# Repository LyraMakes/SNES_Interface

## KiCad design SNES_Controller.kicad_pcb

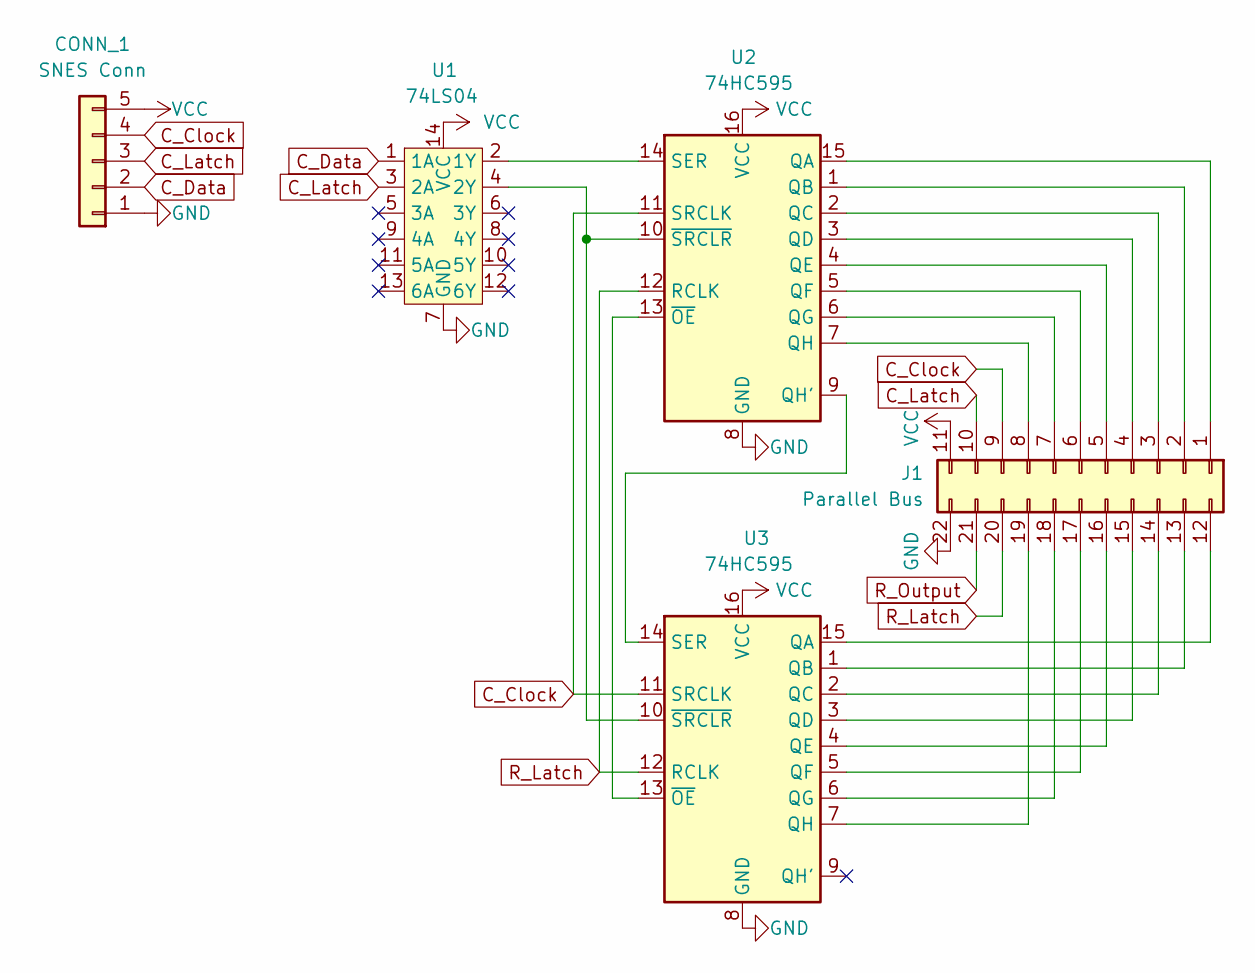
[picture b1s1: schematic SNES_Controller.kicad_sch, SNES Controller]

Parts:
CONN_1: SNES Conn; PinHeader_1x05_P2.54mm_Vertical
J1: Parallel Bus; PinHeader_2x11_P2.54mm_Vertical
U1: 74LS04; DIP-14_W7.62mm
U2, U3: 74HC595; DIP-16_W7.62mm

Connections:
C_Clock: CONN_1.4, J1.9, U2.11 (SRCLK), U3.11 (SRCLK)
C_Data: CONN_1.2, U1.1 (1A)
C_Latch: CONN_1.3, J1.10, U1.3 (2A)
GND: CONN_1.1, J1.22, U1.7 (GND), U2.8 (GND), U3.8 (GND)
unnamed: J1.1, U2.15 (QA)
unnamed: J1.2, U2.1 (QB)
unnamed: J1.3, U2.2 (QC)
unnamed: J1.4, U2.3 (QD)
unnamed: J1.5, U2.4 (QE)
unnamed: J1.6, U2.5 (QF)
unnamed: J1.7, U2.6 (QG)
unnamed: J1.8, U2.7 (QH)
unnamed: J1.12, U3.15 (QA)
unnamed: J1.13, U3.1 (QB)
unnamed: J1.14, U3.2 (QC)
unnamed: J1.15, U3.3 (QD)
unnamed: J1.16, U3.4 (QE)
unnamed: J1.17, U3.5 (QF)
unnamed: J1.18, U3.6 (QG)
unnamed: J1.19, U3.7 (QH)
unnamed: U1.2 (1Y), U2.14 (SER)
unnamed: U2.9 (QH'), U3.14 (SER)
unnamed: U1.4 (2Y), U2.10 (~SRCLR), U3.10 (~SRCLR)
unnamed: U2.13 (~OE), U3.13 (~OE)
R_Latch: J1.20, U2.12 (RCLK), U3.12 (RCLK)
R_Output: J1.21
VCC: CONN_1.5, J1.11, U1.14 (VCC), U2.16 (VCC), U3.16 (VCC)

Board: 2 copper layers, 5 parts (0 on the bottom side), 26 nets, no tracks yet.
